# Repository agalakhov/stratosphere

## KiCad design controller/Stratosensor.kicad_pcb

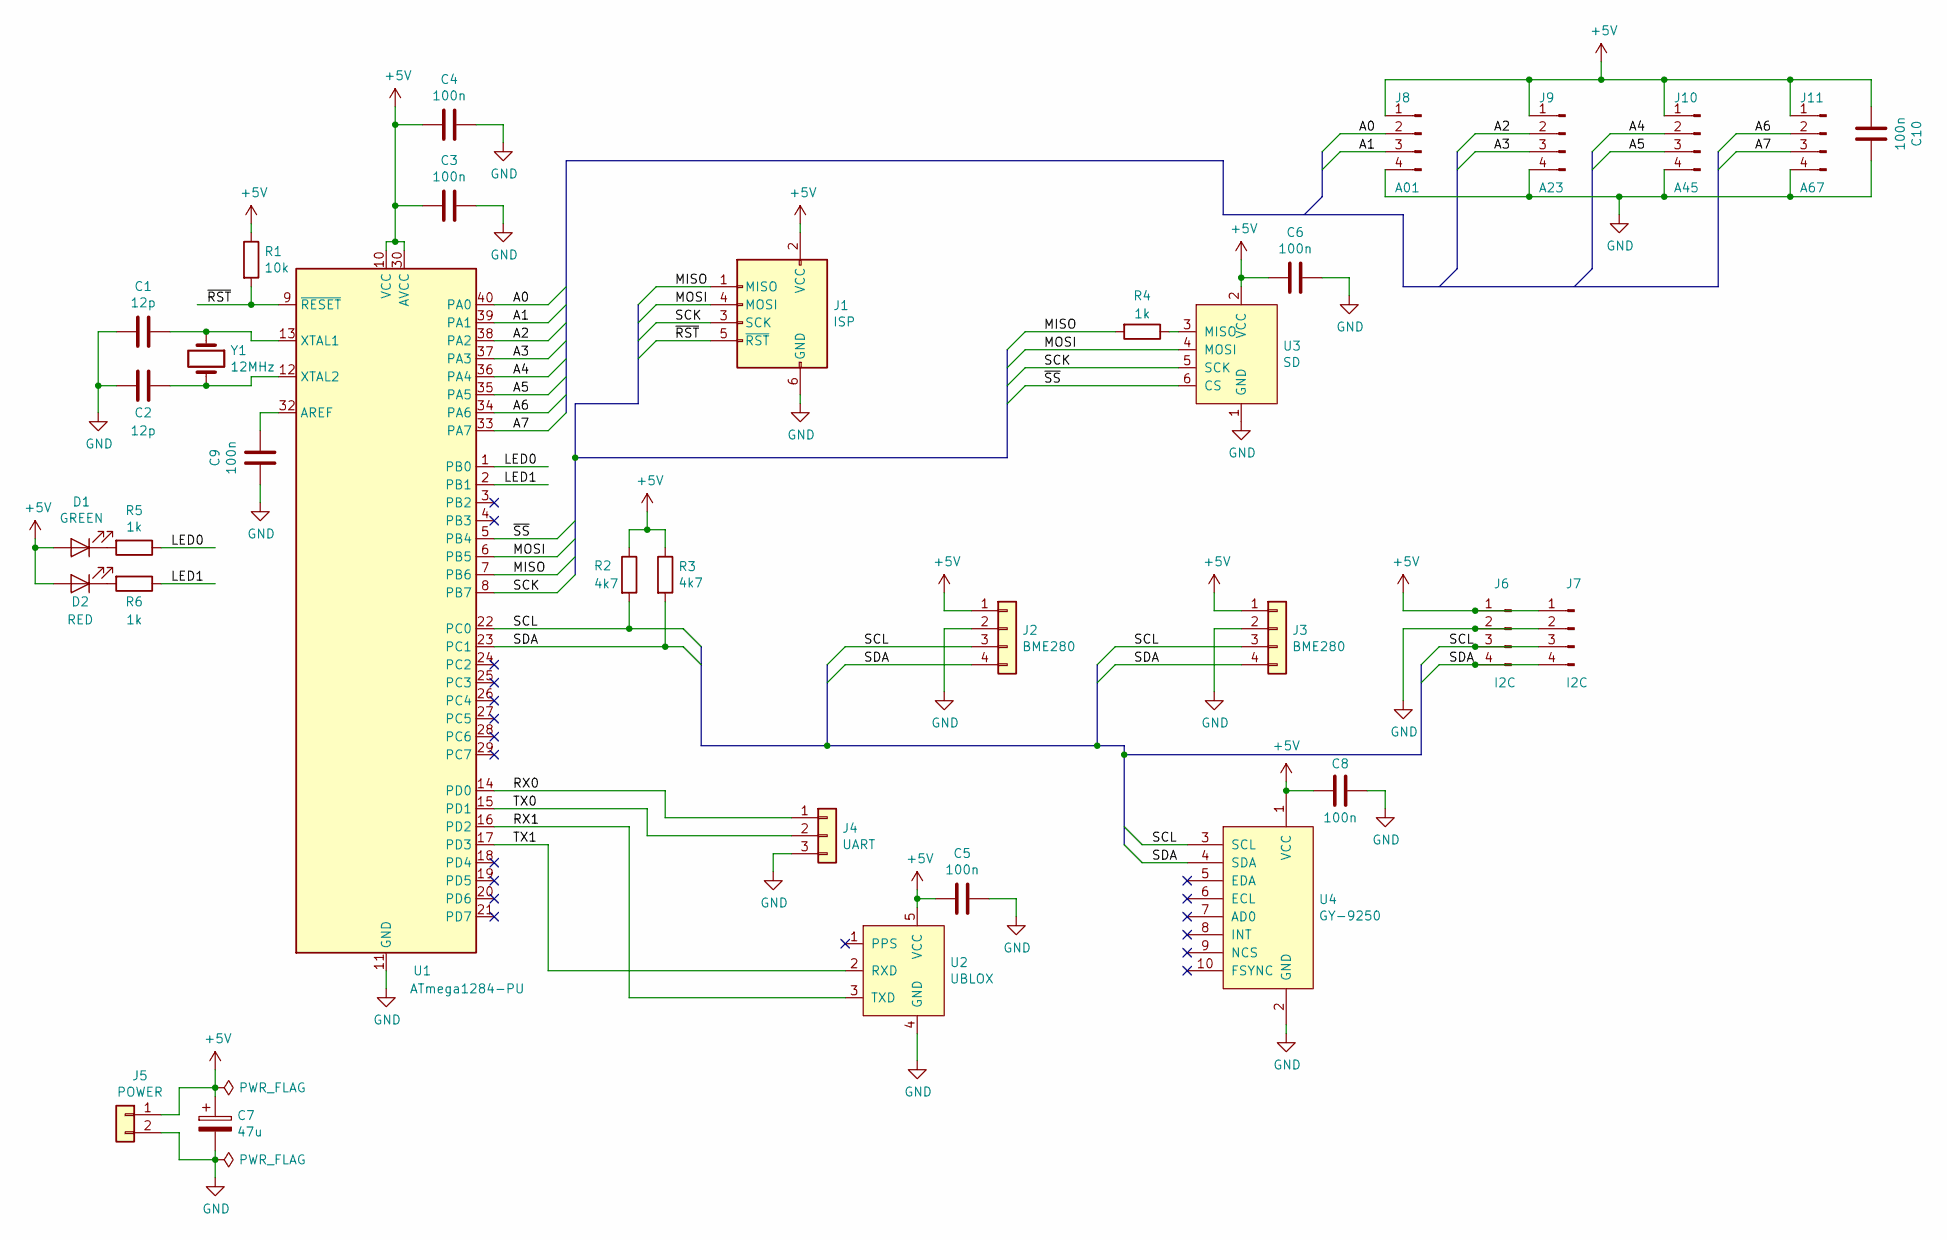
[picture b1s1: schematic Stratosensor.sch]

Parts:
C1, C2: 12p; C_Disc_D4.7mm_W2.5mm_P5.00mm
C3, C4, C5, C6, C8, C9, C10: 100n; C_0805_2012Metric_Pad1.15x1.40mm_HandSolder
C7: 47u; CP_Radial_D6.3mm_P2.50mm
D1: GREEN; LED_D3.0mm_Horizontal_O1.27mm_Z2.0mm
D2: RED; LED_D3.0mm_Horizontal_O1.27mm_Z2.0mm
J1: ISP; IDC-Header_2x03_P2.54mm_Vertical
J2: BME280; PinHeader_1x04_P2.54mm_Vertical
J3: BME280; PinSocket_1x04_P2.54mm_Vertical
J4: UART; PinHeader_1x03_P2.54mm_Vertical
J5: POWER; Molex_KK-254_AE-6410-02A_1x02_P2.54mm_Vertical
J6, J7: I2C; PinHeader_1x04_P2.54mm_Vertical
J8: A01; PinHeader_1x04_P2.54mm_Vertical
J9: A23; PinHeader_1x04_P2.54mm_Vertical
J10: A45; PinHeader_1x04_P2.54mm_Vertical
J11: A67; PinHeader_1x04_P2.54mm_Vertical
R1: 10k; R_Axial_DIN0207_L6.3mm_D2.5mm_P10.16mm_Horizontal
R2, R3: 4k7; R_Axial_DIN0207_L6.3mm_D2.5mm_P10.16mm_Horizontal
R4, R5, R6: 1k; R_Axial_DIN0207_L6.3mm_D2.5mm_P10.16mm_Horizontal
U1: ATmega1284-PU; DIP-40_W15.24mm
U2: UBLOX
U3: SD
U4: GY-9250
Y1: 12MHz; Crystal_HC49-U_Vertical

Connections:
+5V: C3.2, C4.2, C5.2, C6.2, C7.1, C8.2, C10.2, D1.2 (A), D2.2 (A), J1.2 (VCC), J2.1, J3.1, J5.1, J6.1, J7.1, J8.1, J9.1, J10.1, J11.1, R1.1, R2.1, R3.1, U1.10 (VCC), U1.30 (AVCC), U2.5 (VCC), U3.2 (VCC), U4.1 (VCC)
/A0: J8.2, U1.40 (PA0)
/A1: J8.3, U1.39 (PA1)
/A2: J9.2, U1.38 (PA2)
/A3: J9.3, U1.37 (PA3)
/A4: J10.2, U1.36 (PA4)
/A5: J10.3, U1.35 (PA5)
/A6: J11.2, U1.34 (PA6)
/A7: J11.3, U1.33 (PA7)
/LED0: R5.1, U1.1 (PB0)
/LED1: R6.1, U1.2 (PB1)
/MISO: J1.1 (MISO), R4.2, U1.7 (PB6)
/MOSI: J1.4 (MOSI), U1.6 (PB5), U3.4 (MOSI)
/RX0: J4.1, U1.14 (PD0)
/RX1: U1.16 (PD2), U2.3 (TXD)
/SCK: J1.3 (SCK), U1.8 (PB7), U3.5 (SCK)
/SCL: J2.3, J3.3, J6.3, J7.3, R2.2, U1.22 (PC0), U4.3 (SCL)
/SDA: J2.4, J3.4, J6.4, J7.4, R3.2, U1.23 (PC1), U4.4 (SDA)
/TX0: J4.2, U1.15 (PD1)
/TX1: U1.17 (PD3), U2.2 (RXD)
/~RST: J1.5 (~RST), R1.2, U1.9 (~RESET)
/~SS: U1.5 (PB4), U3.6 (CS)
GND: C1.2, C2.2, C3.1, C4.1, C5.1, C6.1, C7.2, C8.1, C9.2, C10.1, J1.6 (GND), J2.2, J3.2, J4.3, J5.2, J6.2, J7.2, J8.4, J9.4, J10.4, J11.4, U1.11 (GND), U1.31 (GND), U2.4 (GND), U3.1 (GND), U4.2 (GND)
unnamed: C1.1, U1.13 (XTAL1), Y1.1
unnamed: C2.1, U1.12 (XTAL2), Y1.2
unnamed: C9.1, U1.32 (AREF)
unnamed: D1.1 (K), R5.2
unnamed: D2.1 (K), R6.2
unnamed: R4.1, U3.3 (MISO)

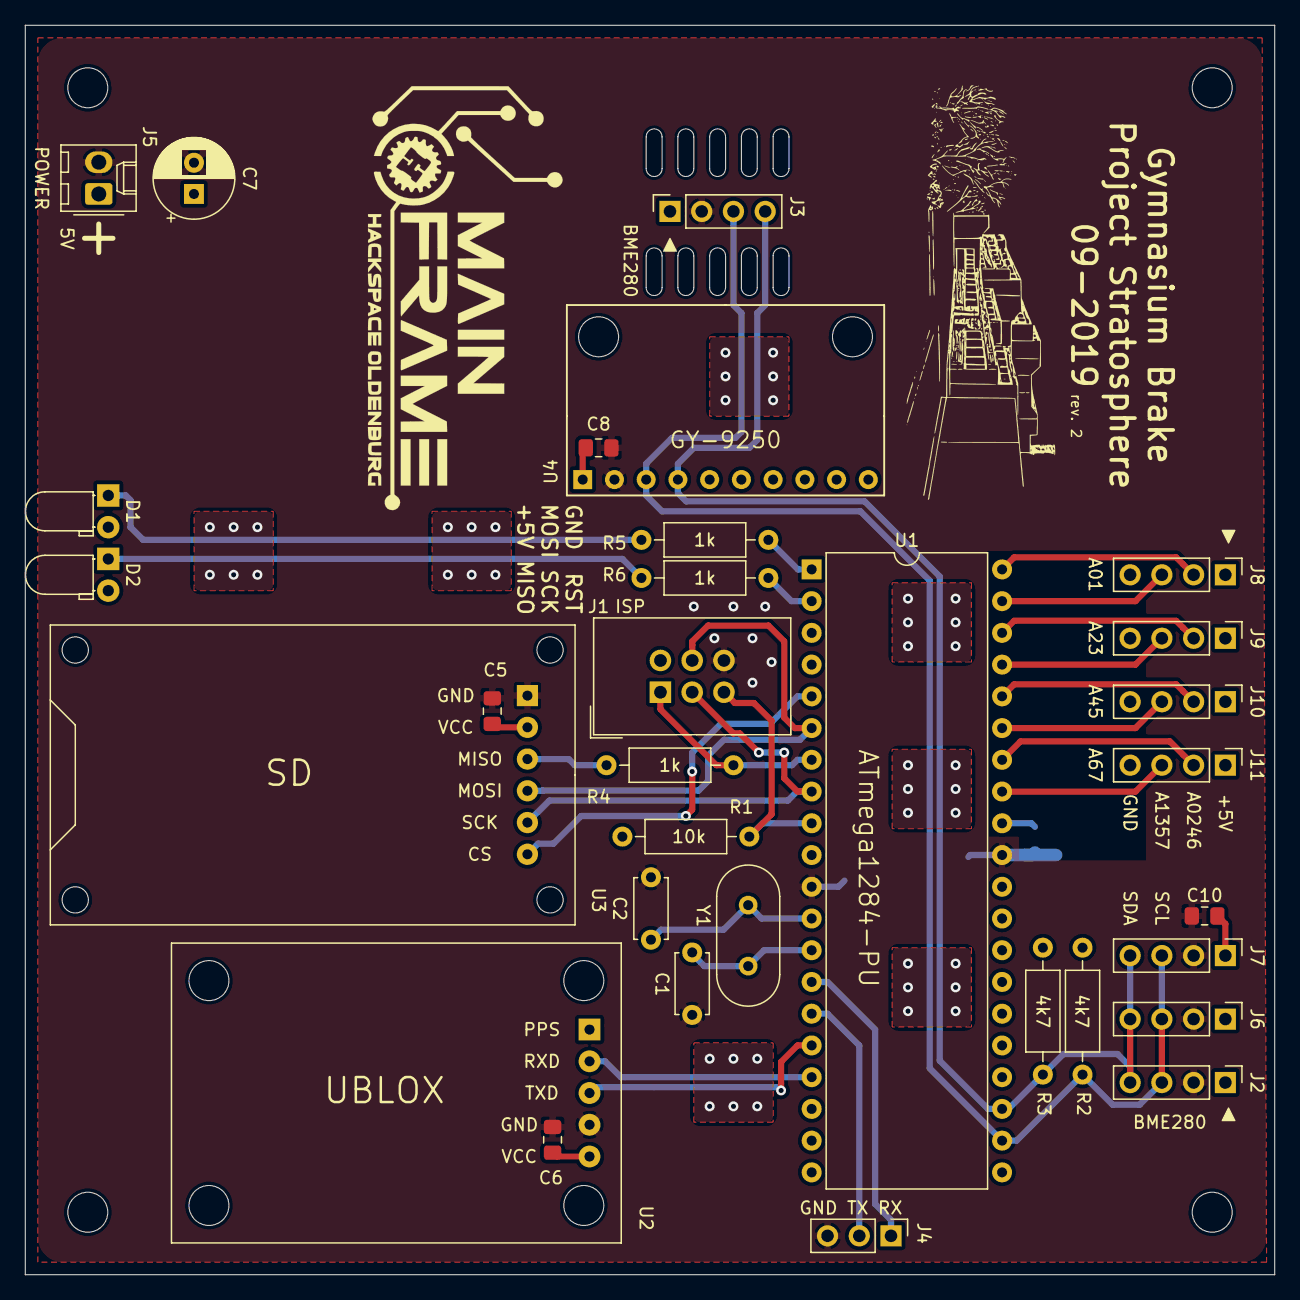
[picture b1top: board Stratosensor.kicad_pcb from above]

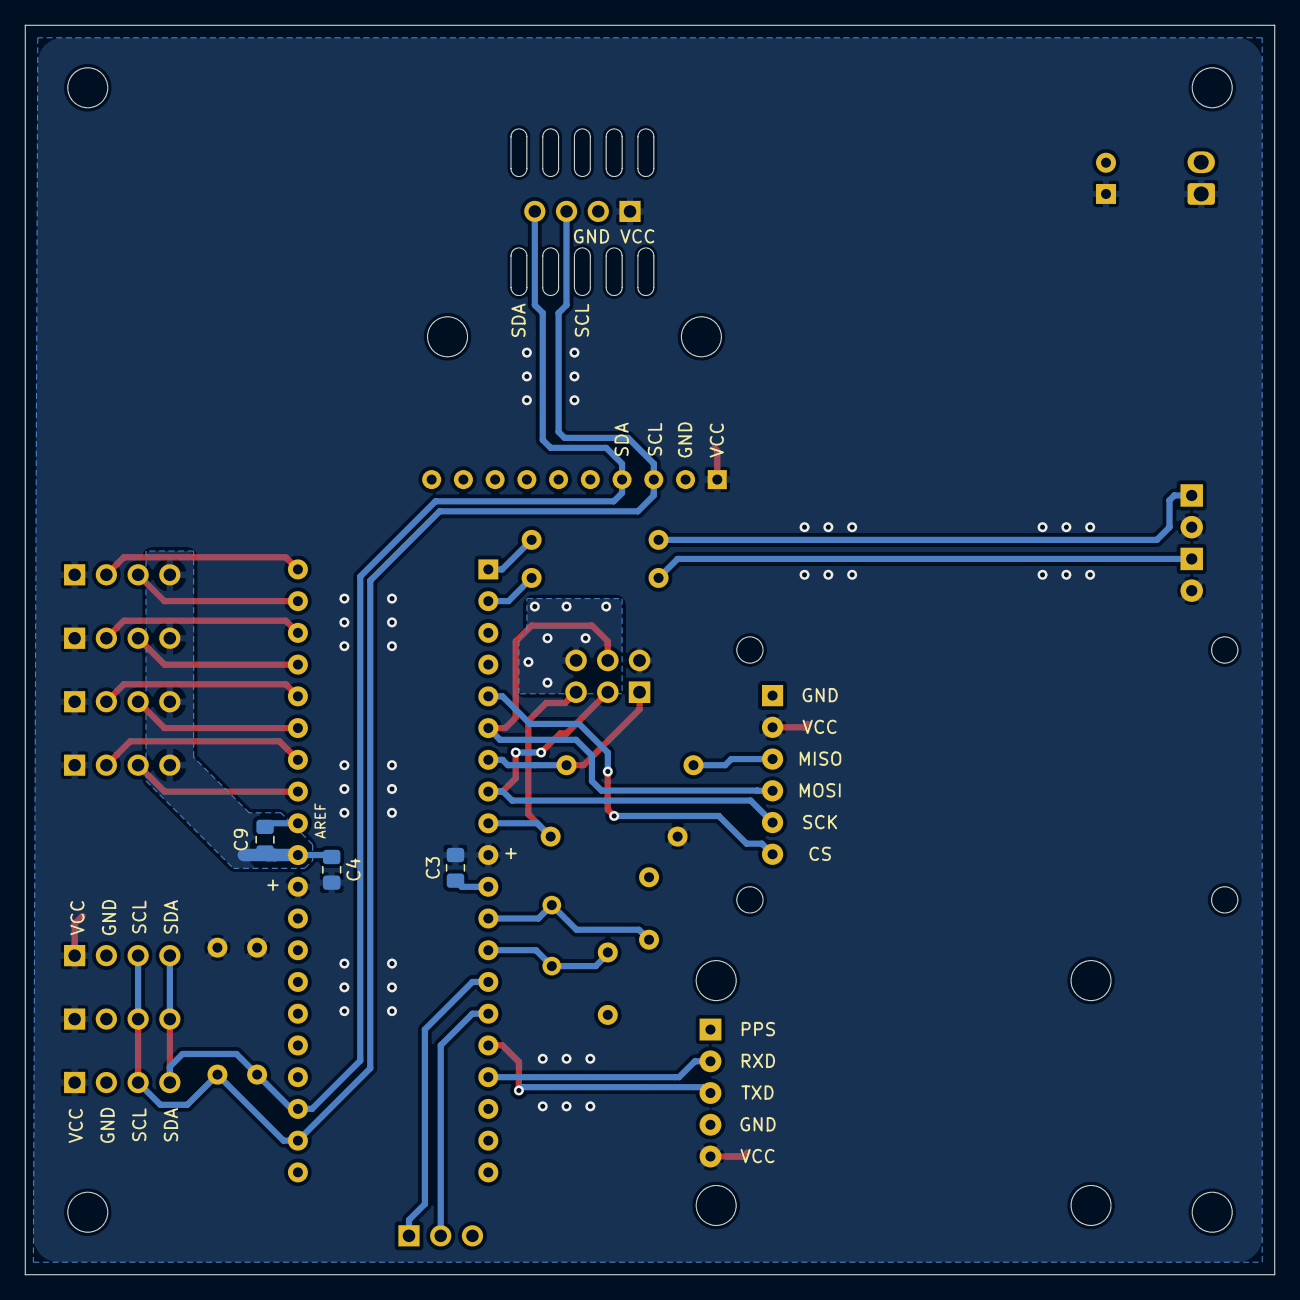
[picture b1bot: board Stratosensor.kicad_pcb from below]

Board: 2 copper layers, 100.0 x 100.0 mm, 35 parts (3 on the bottom side), 29 nets.

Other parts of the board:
e: MountingHole_3.2mm_M3_DIN965

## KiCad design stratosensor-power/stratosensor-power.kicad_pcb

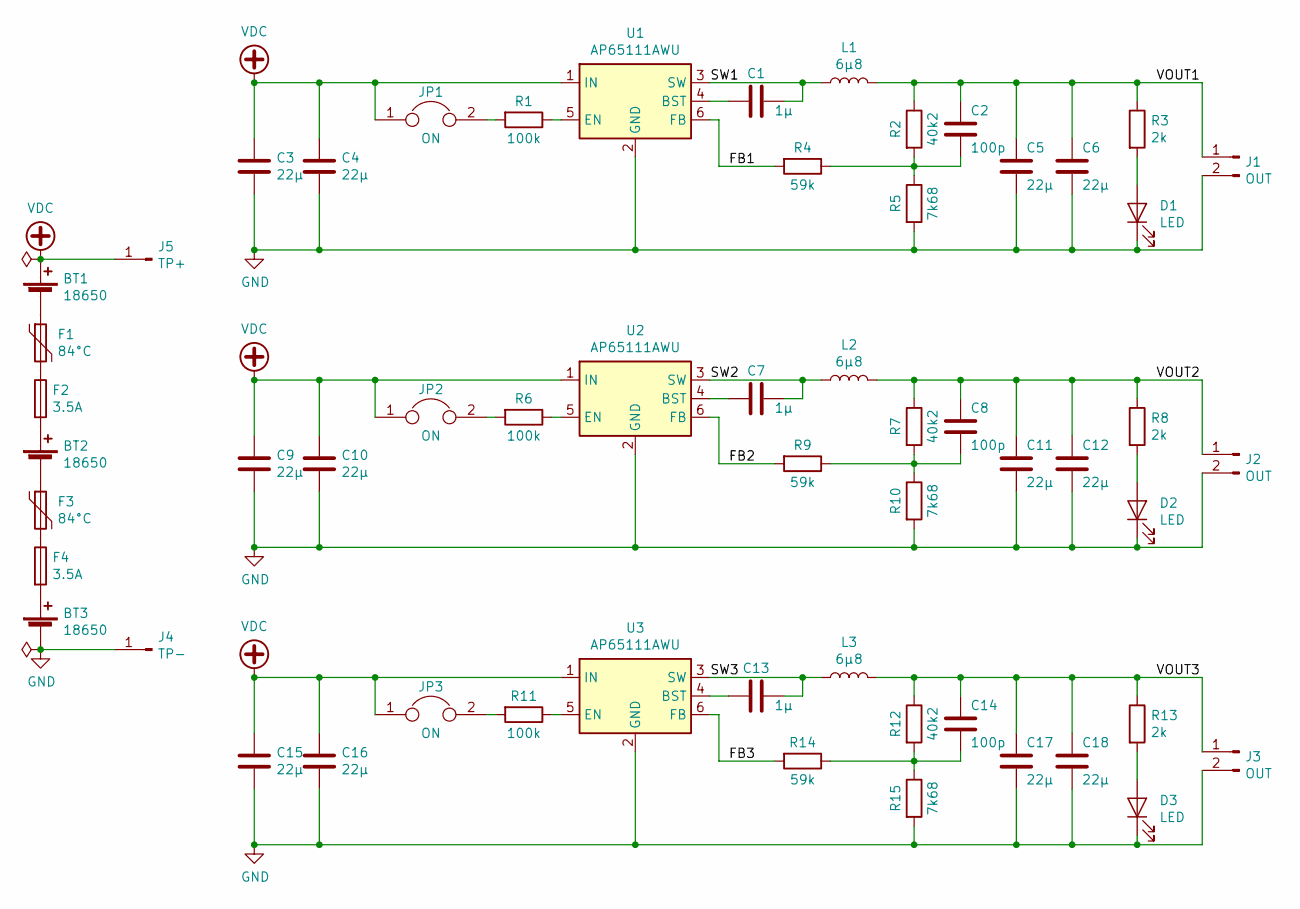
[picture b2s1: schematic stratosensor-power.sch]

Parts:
BT1, BT2, BT3: 18650; BatteryHolder_COMF_BHC-18650-1
C1, C7, C13: 1µ; C_0805_2012Metric_Pad1.15x1.40mm_HandSolder
C2, C8, C14: 100p; C_0805_2012Metric_Pad1.15x1.40mm_HandSolder
C3, C4, C5, C6, C9, C10, C11, C12, C15, C16, C17, C18: 22µ; C_0805_2012Metric_Pad1.15x1.40mm_HandSolder
D1, D2, D3: LED; LED_0805_2012Metric_Pad1.15x1.40mm_HandSolder
F1, F3: 84°C; R_Axial_DIN0411_L9.9mm_D3.6mm_P25.40mm_Horizontal
F2, F4: 3.5A; R_Axial_DIN0309_L9.0mm_D3.2mm_P15.24mm_Horizontal
J1, J2, J3: OUT; Molex_KK-254_AE-6410-02A_1x02_P2.54mm_Vertical
J4: TP-; PinHeader_1x01_P2.54mm_Vertical
J5: TP+; PinHeader_1x01_P2.54mm_Vertical
JP1, JP2, JP3: ON; PinHeader_1x02_P2.54mm_Horizontal
L1, L2, L3: 6µ8; L_Taiyo-Yuden_NR-50xx_HandSoldering
R1, R6, R11: 100k; R_0805_2012Metric_Pad1.15x1.40mm_HandSolder
R2, R7, R12: 40k2; R_0805_2012Metric_Pad1.15x1.40mm_HandSolder
R3, R8, R13: 2k; R_0805_2012Metric_Pad1.15x1.40mm_HandSolder
R4, R9, R14: 59k; R_0805_2012Metric_Pad1.15x1.40mm_HandSolder
R5, R10, R15: 7k68; R_0805_2012Metric_Pad1.15x1.40mm_HandSolder
U1, U2, U3: AP65111AWU; TSOT-23-6

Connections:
/FB1: R4.2, U1.6 (FB)
/FB2: R9.2, U2.6 (FB)
/FB3: R14.2, U3.6 (FB)
/SW1: C1.1, L1.1, U1.3 (SW)
/SW2: C7.1, L2.1, U2.3 (SW)
/SW3: C13.1, L3.1, U3.3 (SW)
/VOUT1: C2.1, C5.1, C6.1, J1.1, L1.2, R2.1, R3.1
/VOUT2: C8.1, C11.1, C12.1, J2.1, L2.2, R7.1, R8.1
/VOUT3: C14.1, C17.1, C18.1, J3.1, L3.2, R12.1, R13.1
GND: BT3.2 (-), C3.2, C4.2, C5.2, C6.2, C9.2, C10.2, C11.2, C12.2, C15.2, C16.2, C17.2, C18.2, D1.1 (K), D2.1 (K), D3.1 (K), J1.2, J2.2, J3.2, J4.1, R5.2, R10.2, R15.2, U1.2 (GND), U2.2 (GND), U3.2 (GND)
unnamed: BT1.2 (-), F1.1
unnamed: BT2.1 (+), F2.2
unnamed: BT2.2 (-), F3.1
unnamed: BT3.1 (+), F4.2
unnamed: C1.2, U1.4 (BST)
unnamed: C2.2, R2.2, R4.1, R5.1
unnamed: C7.2, U2.4 (BST)
unnamed: C8.2, R7.2, R9.1, R10.1
unnamed: C13.2, U3.4 (BST)
unnamed: C14.2, R12.2, R14.1, R15.1
unnamed: D1.2 (A), R3.2
unnamed: D2.2 (A), R8.2
unnamed: D3.2 (A), R13.2
unnamed: F1.2, F2.1
unnamed: F3.2, F4.1
unnamed: JP1.2, R1.2
unnamed: JP2.2, R6.2
unnamed: JP3.2, R11.2
unnamed: R1.1, U1.5 (EN)
unnamed: R6.1, U2.5 (EN)
unnamed: R11.1, U3.5 (EN)
VDC: BT1.1 (+), C3.1, C4.1, C9.1, C10.1, C15.1, C16.1, J5.1, JP1.1, JP2.1, JP3.1, U1.1 (IN), U2.1 (IN), U3.1 (IN)

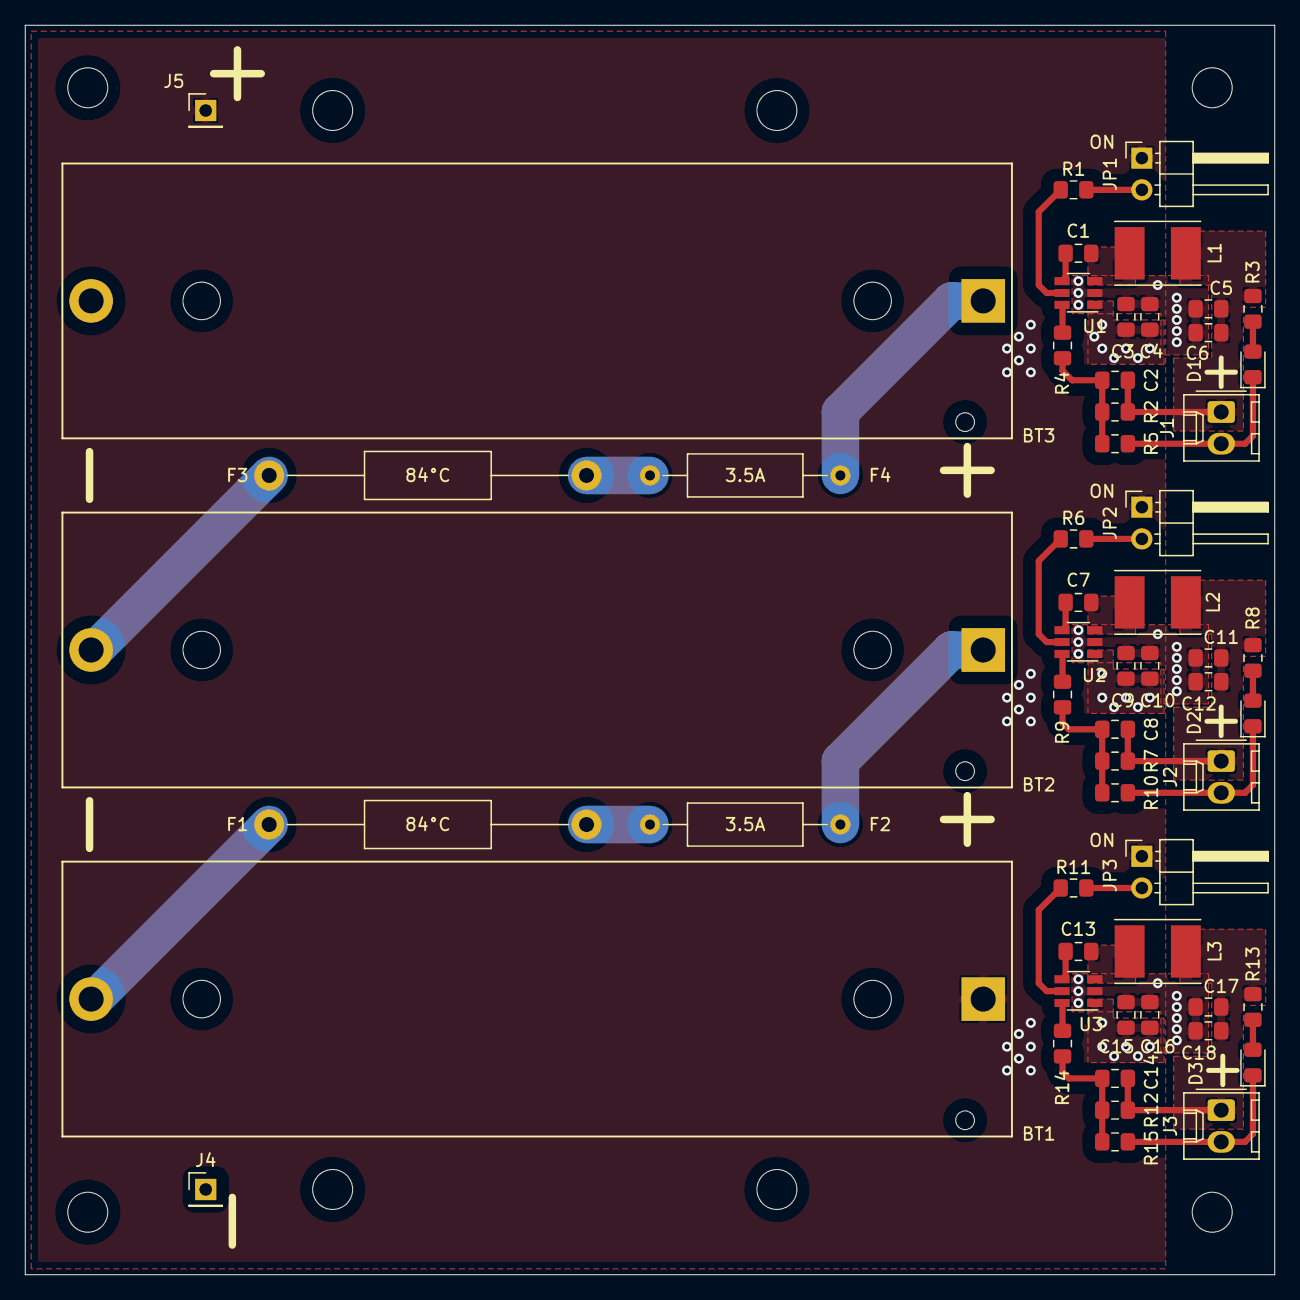
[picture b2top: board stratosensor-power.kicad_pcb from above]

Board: 2 copper layers, 100.0 x 100.0 mm, 57 parts (0 on the bottom side), 32 nets.

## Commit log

2019-08-23 Gerber files
2019-09-24 Add power supply
2019-09-24 add .gitignore
2019-09-25 Revision 2 of controller board
2019-09-25 Finish power board
2019-09-28 Finish and generate gerbers
2019-09-28 Refined v2 and generated gerbers
